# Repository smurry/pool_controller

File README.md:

# Pool Controller
PH and ORP monitor/control for ESP32

To use, you'll need to flash an ESP32 module with micropython.  See: https://micropython.org/download/esp32/.  Version must be May 20,2020 or later.

You must update the conf-example.sample file:
  1)  edit wifi information and mqtt server information as noted in the file.  All values need to be in quotation marks as in the example file.
  2)  save the file with exactly this filename: conf.txt

After saving the conf.txt file, upload conf.txt, config.py, mqtt_as.py and main.py to the ESP32.  If you are unfamiliar with how to do this, check out https://github.com/BetaRavener/uPyLoader

The sensors configured in the conf.txt file represent IO ports on the ESP32-DEVKITC board.  They are designed to work with isolated carrier boards from Atlas Scientific (for example https://www.atlas-scientific.com/carrier-boards/electrically-isolated-ezo-carrier-board-gen-2/).  You will need to purchase the carrier boards, EZO modules, and probes from Atlas.

Outputs are provided on the IO ports noted in the conf.txt file for Ph Pump (i.e. acid) and ORP Pump (i.e. bleach).  These pins can be connected through appropriate isolation and relays to peristaltic pumps used to dispense the required chemicals into the pool.

This system was designed to work with Home Assistant, although in principle any MQTT-enabled controller should work.  Configuration files for Home Assistant are in the directory "Home Assistant."  The .yaml package goes into your packages directory and the pool_fc.py is an appdaemon file and should go in the appropriate appdaemon folder.

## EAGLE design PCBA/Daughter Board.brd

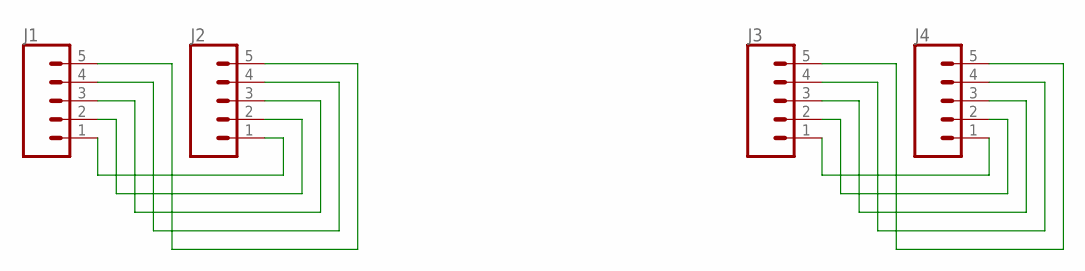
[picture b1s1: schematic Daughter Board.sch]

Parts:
J1, J2, J3, J4: CONN_05; 1X05

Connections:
unnamed: J1.1, J2.1
unnamed: J1.2, J2.2
unnamed: J1.3, J2.3
unnamed: J1.4, J2.4
unnamed: J1.5, J2.5
unnamed: J3.1, J4.1
unnamed: J3.2, J4.2
unnamed: J3.3, J4.3
unnamed: J3.4, J4.4
unnamed: J3.5, J4.5

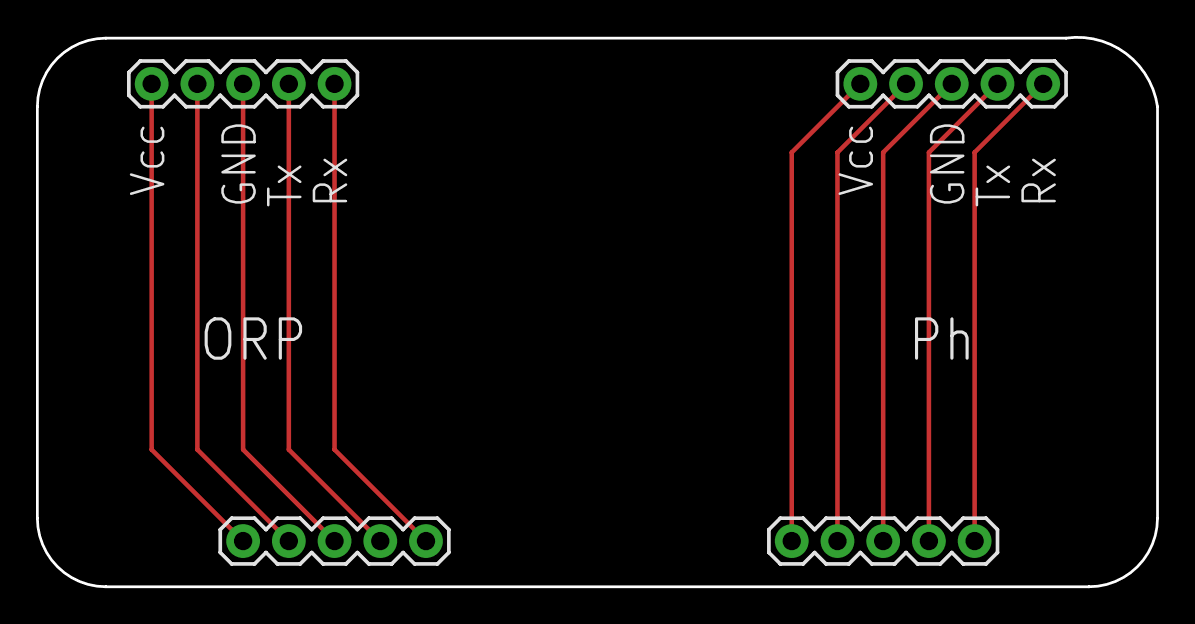
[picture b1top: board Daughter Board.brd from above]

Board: 2 copper layers, 62.2 x 30.5 mm, 4 parts (0 on the bottom side), 10 nets.

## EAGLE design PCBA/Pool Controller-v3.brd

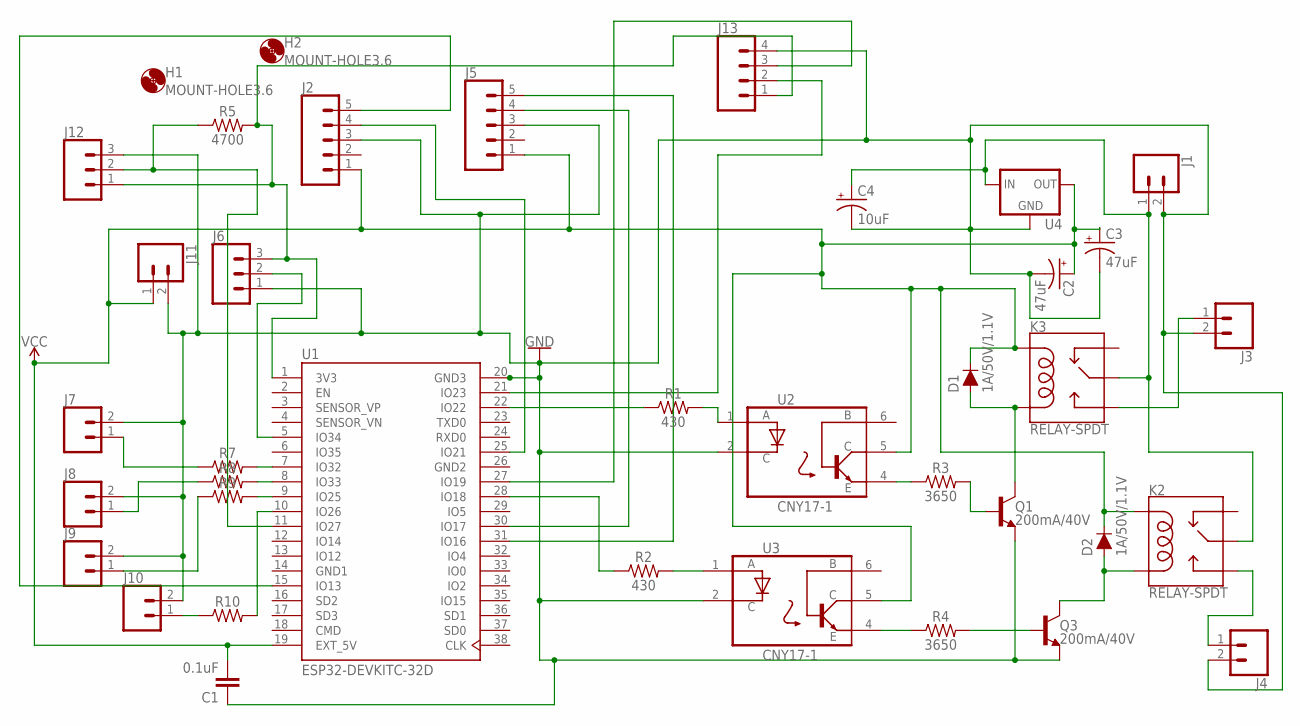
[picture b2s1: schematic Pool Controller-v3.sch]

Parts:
C1: 0.1uF; CAP-PTH-SMALL-KIT
C2: 47uF; CPOL-RADIAL-2.5MM-5MM-KIT
C3: 47uF; CPOL-RADIAL-2.5MM-5MM
C4: 10uF; CPOL-RADIAL-2.5MM-5MM
D1, D2: 1A/50V/1.1V; DIODE-1N4001
H1, H2: MOUNT-HOLE3.6; 3,6
J1, J3, J4, J11: CONN_023.5MM; SCREWTERMINAL-3.5MM-2
J2, J5: CONN_05; 1X05
J6, J12: CONN_03SCREW; SCREWTERMINAL-3.5MM-3
J7, J8, J9, J10: CONN_02; 1X02
J13: CONN_04SCREW; SCREWTERMINAL-3.5MM-4
K2, K3: RELAY-SPDT; RELAY_G5LE
Q1, Q3: 200mA/40V; TO-92
R1, R2: 430; AXIAL-0.3
R3, R4: 3650; AXIAL-0.3
R5: 4700; AXIAL-0.3
R7, R8, R9, R10: AXIAL-0.3
U1: ESP32-DEVKITC-32D; MODULE_ESP32-DEVKITC-32D
U2, U3: CNY17-1; DIP762W50P254L730H410Q6
U4: V_REG_78XXSIDE; 78XXL

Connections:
GND: C1.1, C2.2 (-), C3.2 (-), C4.2 (-), J1.2, J2.3, J3.2, J4.2, J5.3, J6.1, J7.2, J8.2, J9.2, J10.2, J11.2, J12.3, J13.4, Q1.1 (E), Q3.1 (E), U1.20 (GND3), U2.2 (C), U3.2 (C), U4.GND
GND1: U1.14 (GND1)
GND2: U1.26 (GND2)
unnamed: R2.P$2 (2), U3.1 (A)
unnamed: R1.P$1 (1), U1.22 (IO22)
unnamed: R1.P$2 (2), U2.1 (A)
unnamed: R2.P$1 (1), U1.28 (IO18)
unnamed: R3.P$1 (1), U2.4 (E)
unnamed: Q1.2 (B), R3.P$2 (2)
unnamed: D1.A, K3.5 (COIL2), Q1.3 (C)
unnamed: C4.1 (+), J1.1, K2.1 (MAIN), K3.1 (MAIN), U4.IN
unnamed: J5.4, U1.30 (IO17)
unnamed: J3.1, K3.3 (NO)
unnamed: J6.3, J12.1, J13.1, R5.P$2 (2), U1.1 (3V3)
unnamed: D2.A, K2.5 (COIL2), Q3.3 (C)
unnamed: J4.1, K2.3 (NO)
unnamed: R4.P$1 (1), U3.4 (E)
unnamed: Q3.2 (B), R4.P$2 (2)
unnamed: J6.2, U1.5 (IO34)
unnamed: J2.5, U1.15 (IO13)
unnamed: J2.4, U1.25 (IO21)
unnamed: J5.5, U1.31 (IO16)
unnamed: J12.2, R5.P$1 (1), U1.11 (IO27)
unnamed: R7.P$2 (2), U1.7 (IO32)
unnamed: J7.1, R7.P$1 (1)
unnamed: R8.P$2 (2), U1.8 (IO33)
unnamed: J8.1, R8.P$1 (1)
unnamed: R9.P$2 (2), U1.9 (IO25)
unnamed: J9.1, R9.P$1 (1)
unnamed: J10.1, R10.P$1 (1)
unnamed: R10.P$2 (2), U1.10 (IO26)
unnamed: J13.3, U1.27 (IO19)
unnamed: J13.2, U1.21 (IO23)
VCC: C1.2, C2.1 (+), C3.1 (+), D1.C, D2.C, J2.1, J5.1, J11.1, K2.2 (COIL1), K3.2 (COIL1), U1.19 (EXT_5V), U2.5 (C`), U3.5 (C`), U4.OUT

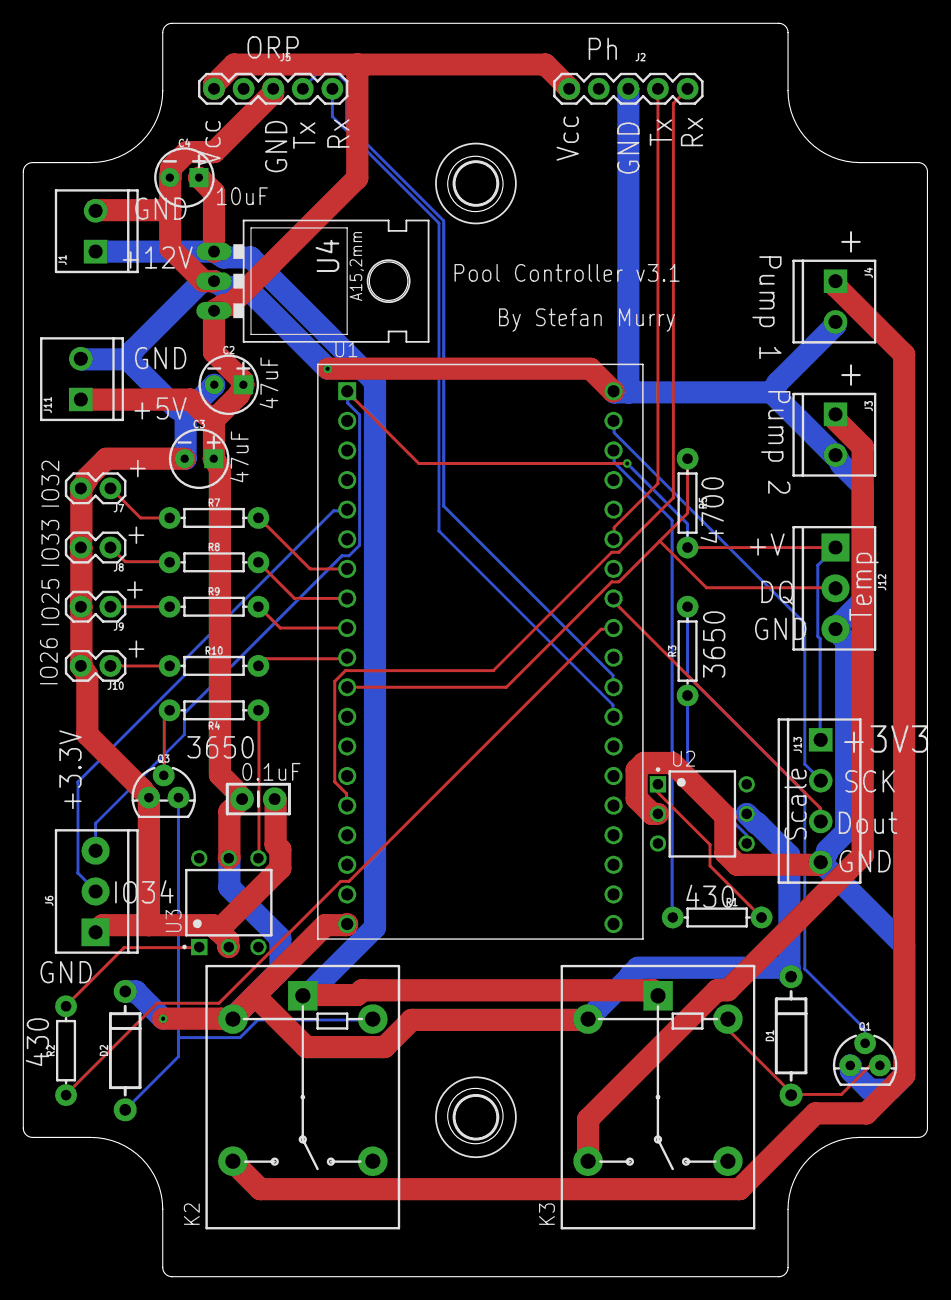
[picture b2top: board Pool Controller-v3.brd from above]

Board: 2 copper layers, 77.6 x 107.6 mm, 38 parts (0 on the bottom side), 32 nets.

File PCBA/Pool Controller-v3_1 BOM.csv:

Qty,Value,Device,Package,Parts,Digikey P/N,Price (USD),Line (USD)
4,,Screw Terminal Connector - 2 places,SCREWTERMINAL-3.5MM-2,"J1, J3, J4, J11",609-4725-ND,0.69,2.76
2,,Screw Terminal Connector - 3 places,SCREWTERMINAL-3.5MM-3,"J6, J12",ED2741-ND,0.42,0.84
2,,Screw Terminal Connector - 4 places,SCREWTERMINAL-3.5MM-4,J13,use 2 609-4725-ND,0.69,1.38
1,,Switching Regulator-5.5V-TPSM84205EAB,78XXL,U4,296-47074-ND,5.43,5.43
4,280,Axial Resistor-280 ohm,AXIAL-0.3,"R7, R8, R9, R10",280XBK-ND ,0.04,0.16
1,0.1uF,Radial Capacitor - 0.1 uF,CAP-PTH-SMALL-KIT,C1,399-9859-1-ND,0.16,0.16
2,47uF,Radial Ceramic Capacitor - 47 uF,CPOL-RADIAL-2.5MM-5MM-KIT,"C2, C3",445-173152-1-ND,1.09,2.18
1,10uF,Radial Capacitor - 10 uF,CPOL-RADIAL-2.5MM-5MM-KIT,C4,399-3565-ND,1.50,1.50
2,1A/50V/1.1V,Radial Diode-1N4001,DIODE-1N4001,"D1, D2",641-1310-1-ND,0.09,0.17
2,200mA/40V,NPN Transistor -2N3904,TO-92,"Q1, Q3",2N3904FS-ND,0.16,0.32
2,3650,Axial Resistor-3650 ohm,AXIAL-0.3,"R3, R4",3.65KXBK-ND,0.06,0.11
2,430,Axial Resistor-430 ohm,AXIAL-0.3,"R1, R2",432XBK-ND,0.06,0.11
1,4700,Axial Resistor-4700 ohm,AXIAL-0.3,R5,4.75KXBK-ND,0.06,0.06
2,CNY17-1,Optoisolator - CNY17-1,DIP762W50P254L730H410Q6,"U2, U3",160-1308-5-ND,0.38,0.75
1,ESP32-DEVKITC-32D,ESP32-DEVKITC-32D,MODULE_ESP32-DEVKITC-32D,U1,1965-ESP32-DEVKITC-32UE-ND,10.00,10.00
2,RELAY-SPDT,Relay - SPDT,RELAY_G5LE,"K2, K3",Z1011-ND,1.35,2.70
2,,5 position header,,"J2, J5",S6103-ND,0.47,0.94
1,623nm,Red LED,,J10,160-1087-ND,0.36,0.36
,,,,,,,29.94

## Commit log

2020-06-24 Create LICENSE
2020-06-24 Added example conf file.
2020-06-24 Fixed typo
2020-06-24 Fixed another typo
2020-06-25 added config for load cell
2020-07-07 Added PCBA Gerber and Eagle files.
2020-07-07 Added Daughter Board
2020-07-07 Added PCBA BOM

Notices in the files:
parts and their libraries:
SparkFun-Connectors: Licensing: Creative Commons ShareAlike 4.0 International - https://creativecommons.org/licenses/by-sa/4.0
